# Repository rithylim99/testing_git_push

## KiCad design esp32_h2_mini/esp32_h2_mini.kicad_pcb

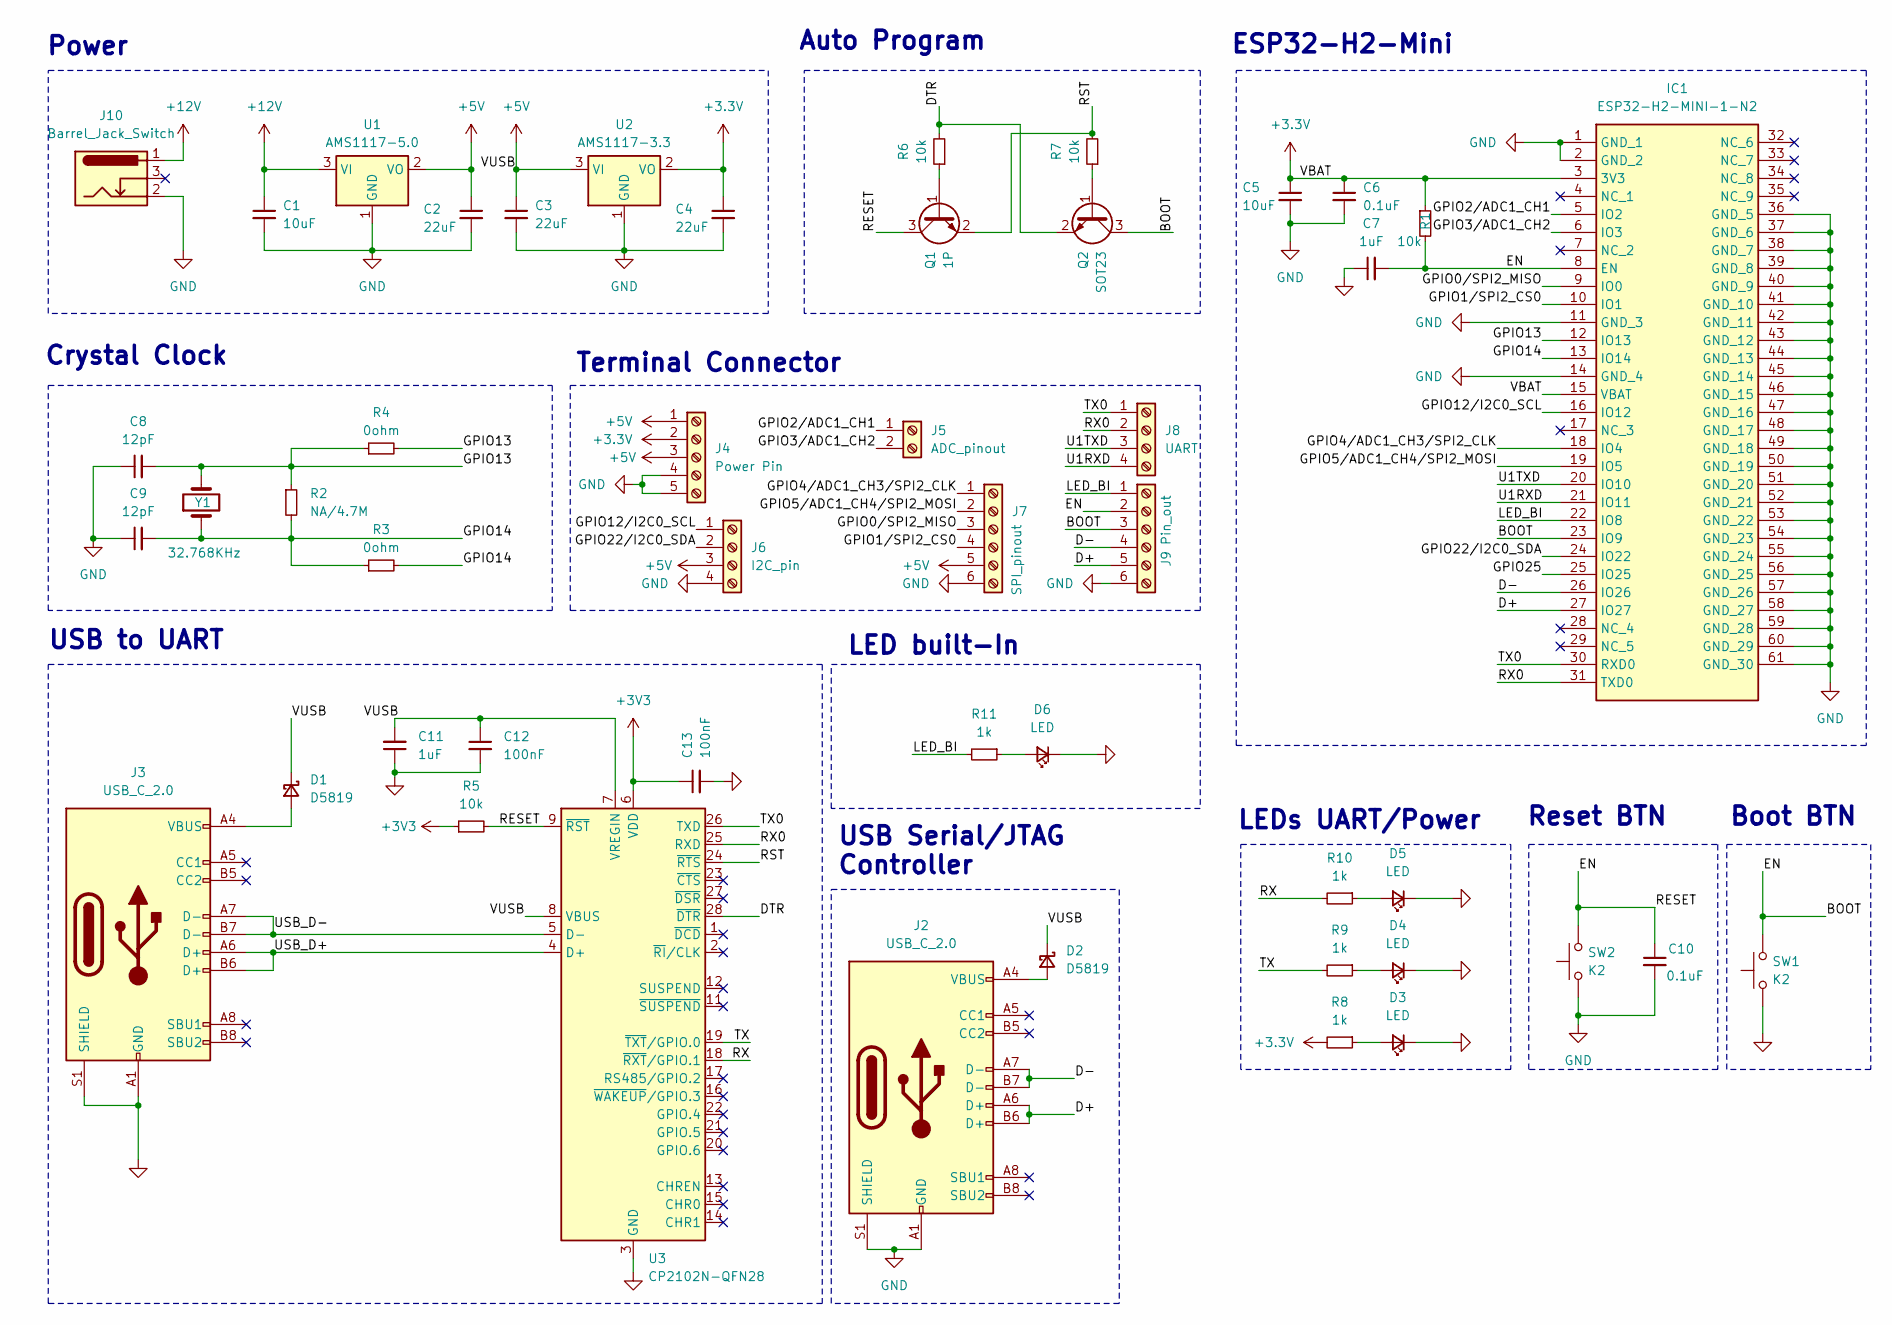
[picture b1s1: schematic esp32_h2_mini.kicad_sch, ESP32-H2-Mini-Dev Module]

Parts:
C1: 10uF; C_0805_2012Metric
C2, C3, C4: 22uF; C_0805_2012Metric
C5: 10uF; C_0603_1608Metric
C6, C10: 0.1uF; C_0603_1608Metric
C7, C11: 1uF; C_0603_1608Metric
C8, C9: 12pF; C_0603_1608Metric
C12, C13: 100nF; C_0603_1608Metric
D1, D2: D5819; D_SOD-123
D3, D4, D5, D6: LED; LED_0603_1608Metric
IC1: ESP32-H2-MINI-1-N2; ESP32H2MINI1N2; Mouser Part Number 356-ESP32H2MINI1-N2
J2, J3: USB_C_2.0; USB_C_Receptacle_Palconn_UTC16-G
J4: Power Pin; PinSocket_1x05_P2.54mm_Vertical
J5: ADC_pinout; PinSocket_1x02_P2.54mm_Vertical
J6: I2C_pin; PinSocket_1x04_P2.54mm_Vertical
J7: SPI_pinout; PinSocket_1x06_P2.54mm_Vertical
J8: UART; PinSocket_1x04_P2.54mm_Vertical
J9: Pin_out; PinSocket_1x06_P2.54mm_Vertical
J10: Barrel_Jack_Switch; BarrelJack_Horizontal
Q1: 1P; SOT-23
Q2: SOT23; SOT-23
R1, R5, R6, R7: 10k; R_0603_1608Metric
R2: NA/4.7M; R_0603_1608Metric
R3, R4: 0ohm; R_0603_1608Metric
R8, R9, R10, R11: 1k; R_0603_1608Metric
SW1, SW2: K2; SW_Push_1P1T_NO_Vertical_Wuerth_434133025816
U1: AMS1117-5.0; SOT-223-3_TabPin2
U2: AMS1117-3.3; SOT-223-3_TabPin2
U3: CP2102N-QFN28; QFN-28-1EP_5x5mm_P0.5mm_EP3.35x3.35mm
Y1: 32.768KHz; Crystal_SMD_3215-2Pin_3.2x1.5mm

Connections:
+3.3V: C4.1, C5.1, C6.1, IC1.3 (3V3), IC1.15 (VBAT), J4.2, R1.1, R8.2, U2.2 (VO)
+3V3: C13.1, R5.1, U3.6 (VDD)
+5V: C2.1, C3.1, C11.2, C12.1, D1.1 (K), D2.1 (K), J4.1, J4.3, J6.3, J7.5, U1.2 (VO), U2.3 (VI), U3.7 (VREGIN), U3.8 (VBUS)
+12V: C1.1, J10.1, U1.3 (VI)
/BOOT: C7.2, C10.1, IC1.8 (EN), IC1.23 (IO9), J9.2, J9.3, Q1.3 (C), Q2.3 (C), R1.2, R5.2, SW1.2, SW2.2, U3.9 (~RST)
/D+: IC1.27 (IO27), J2.A6 (D+), J2.B6 (D+), J9.5
/D-: IC1.26 (IO26), J2.A7 (D-), J2.B7 (D-), J9.4
/DTR: Q2.2 (E), R6.2, U3.28 (~DTR)
/GPIO0/SPI2_MISO: IC1.9 (IO0), J7.3
/GPIO1/SPI2_CS0: IC1.10 (IO1), J7.4
/GPIO2/ADC1_CH1: IC1.5 (IO2), J5.1
/GPIO3/ADC1_CH2: IC1.6 (IO3), J5.2
/GPIO4/ADC1_CH3/SPI2_CLK: IC1.18 (IO4), J7.1
/GPIO5/ADC1_CH4/SPI2_MOSI: IC1.19 (IO5), J7.2
/GPIO12/I2C0_SCL: IC1.16 (IO12), J6.1
/GPIO13: C8.2, IC1.12 (IO13), R2.1, R4.1, R4.2, Y1.2
/GPIO14: C9.2, IC1.13 (IO14), R2.2, R3.1, R3.2, Y1.1
/GPIO22/I2C0_SDA: IC1.24 (IO22), J6.2
/GPIO25: IC1.25 (IO25)
/LED_BI: IC1.22 (IO8), J9.1, R11.2
/RST: Q1.2 (E), R7.2, U3.24 (~RTS)
/RX: R10.2, U3.18 (~RXT/GPIO.1)
/RX0: IC1.31 (TXD0), J8.2, U3.25 (RXD)
/TX: R9.2, U3.19 (~TXT/GPIO.0)
/TX0: IC1.30 (RXD0), J8.1, U3.26 (TXD)
/U1RXD: IC1.21 (IO11), J8.4
/U1TXD: IC1.20 (IO10), J8.3
/USB_D+: J3.A6 (D+), J3.B6 (D+), U3.4 (D+)
/USB_D-: J3.A7 (D-), J3.B7 (D-), U3.5 (D-)
GND: C1.2, C2.2, C3.2, C4.2, C5.2, C6.2, C7.1, C8.1, C9.1, C10.2, C11.1, C12.2, C13.2, D3.1 (K), D4.1 (K), D5.1 (K), D6.1 (K), IC1.1 (GND_1), IC1.2 (GND_2), IC1.11 (GND_3), IC1.14 (GND_4), IC1.36 (GND_5), IC1.37 (GND_6), IC1.38 (GND_7), IC1.39 (GND_8), IC1.40 (GND_9), IC1.41 (GND_10), IC1.42 (GND_11), IC1.43 (GND_12), IC1.44 (GND_13), IC1.45 (GND_14), IC1.46 (GND_15), IC1.47 (GND_16), IC1.48 (GND_17), IC1.49 (GND_18), IC1.50 (GND_19), IC1.51 (GND_20), IC1.52 (GND_21), IC1.53 (GND_22), IC1.54 (GND_23), IC1.55 (GND_24), IC1.56 (GND_25), IC1.57 (GND_26), IC1.58 (GND_27), IC1.59 (GND_28), IC1.60 (GND_29), IC1.61 (GND_30), J2.A1 (GND), J2.A12 (GND), J2.B1 (GND), J2.B12 (GND), J2.S1 (SHIELD), J3.A1 (GND), J3.A12 (GND), J3.B1 (GND), J3.B12 (GND), J3.S1 (SHIELD), J4.4, J4.5, J6.4, J7.6, J9.6, J10.2, SW1.1, SW2.1, U1.1 (GND), U2.1 (GND), U3.3 (GND), U3.29 (GND)
unnamed: D1.2 (A), J3.A4 (VBUS), J3.A9 (VBUS), J3.B4 (VBUS), J3.B9 (VBUS)
unnamed: D2.2 (A), J2.A4 (VBUS), J2.A9 (VBUS), J2.B4 (VBUS), J2.B9 (VBUS)
unnamed: D3.2 (A), R8.1
unnamed: D4.2 (A), R9.1
unnamed: D5.2 (A), R10.1
unnamed: D6.2 (A), R11.1
unnamed: Q1.1 (B), R6.1
unnamed: Q2.1 (B), R7.1

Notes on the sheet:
LED built-In
Crystal Clock
Boot BTN
Power
Auto Program
USB to UART
ESP32-H2-Mini
LEDs UART/Power
Reset BTN
USB Serial/JTAG Controller
Terminal Connector

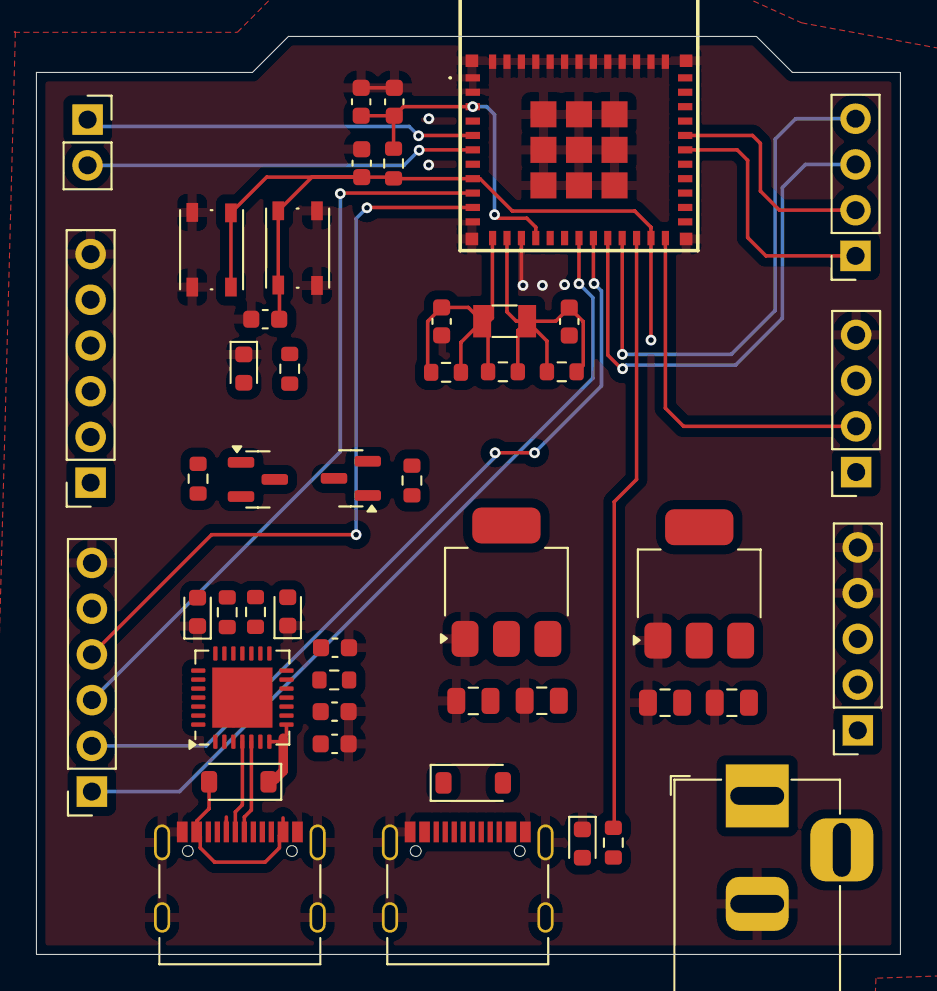
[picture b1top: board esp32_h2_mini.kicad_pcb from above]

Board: 2 copper layers, 48.0 x 51.0 mm, 48 parts (0 on the bottom side), 37 nets.

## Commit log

2024-03-15 KiCad
